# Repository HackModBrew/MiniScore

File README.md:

# MiniScore
Handheld scoreboard, dice roller, and timer.

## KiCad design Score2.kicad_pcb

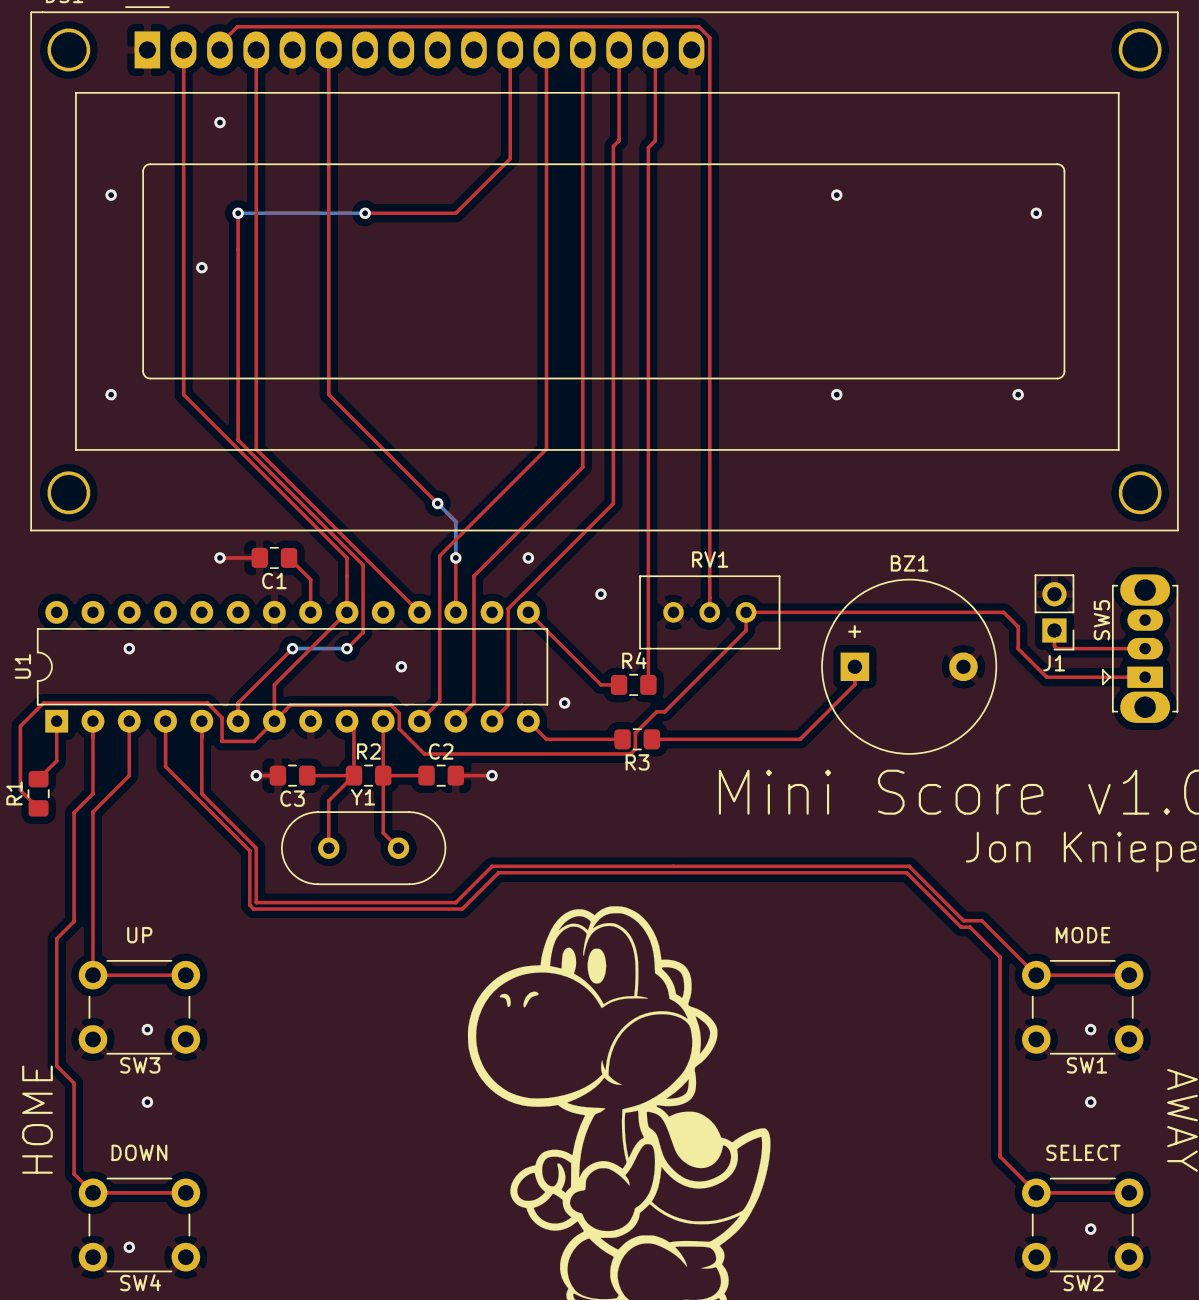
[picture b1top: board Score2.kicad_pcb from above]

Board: 2 copper layers, 18 parts (0 on the bottom side), 22 nets.

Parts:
BZ1: Buzzer; Buzzer_12x9.5RM7.6
C1, C2, C3: C; C_0805_2012Metric_Pad1.15x1.40mm_HandSolder
DS1: WC1602A
J1: Conn_01x02_Female; PinHeader_1x02_P2.54mm_Vertical
R1: 10k; R_0805_2012Metric_Pad1.15x1.40mm_HandSolder
R2: 1M; R_0805_2012Metric_Pad1.15x1.40mm_HandSolder
R3: 100; R_0805_2012Metric_Pad1.15x1.40mm_HandSolder
R4: 220; R_0805_2012Metric_Pad1.15x1.40mm_HandSolder
RV1: 10k; Potentiometer_Bourns_3296W_Vertical
SW1, SW2, SW3, SW4: SW_SPST; SW_PUSH_6mm
SW5: SW_SPST; SW_Slide_1P2T_CK_OS102011MS2Q
U1: ATmega328P-PU; DIP-28_W7.62mm
Y1: Crystal; Crystal_HC49-4H_Vertical

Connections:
+5V: DS1.2, R1.1, RV1.1, SW5.1, U1.7, U1.20
GND: BZ1.2, C1.2, C2.2, C3.2, DS1.1, DS1.5, DS1.16, J1.2, RV1.3, SW1.2, SW2.2, SW3.2, SW4.2, U1.8, U1.22
unnamed: BZ1.1, R3.1
unnamed: C1.1, U1.21
unnamed: C2.1, R2.2, U1.10, Y1.2
unnamed: C3.1, R2.1, U1.9, Y1.1
unnamed: DS1.3, RV1.2
unnamed: DS1.4, U1.18
unnamed: DS1.6, U1.17
unnamed: DS1.11, U1.6
unnamed: DS1.12, U1.11
unnamed: DS1.13, U1.12
unnamed: DS1.14, U1.13
unnamed: DS1.15, R4.2
unnamed: J1.1, SW5.2
unnamed: R1.2, U1.1
unnamed: R3.2, U1.14
unnamed: R4.1, U1.15
unnamed: SW1.1, U1.5
unnamed: SW2.1, U1.4
unnamed: SW3.1, U1.3
unnamed: SW4.1, U1.2

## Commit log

2020-01-20 Score Schematic and Board
2020-01-20 MasterCode
    Code for all functions
2020-01-20 Score Only Code
2020-01-20 Update MasterCode
